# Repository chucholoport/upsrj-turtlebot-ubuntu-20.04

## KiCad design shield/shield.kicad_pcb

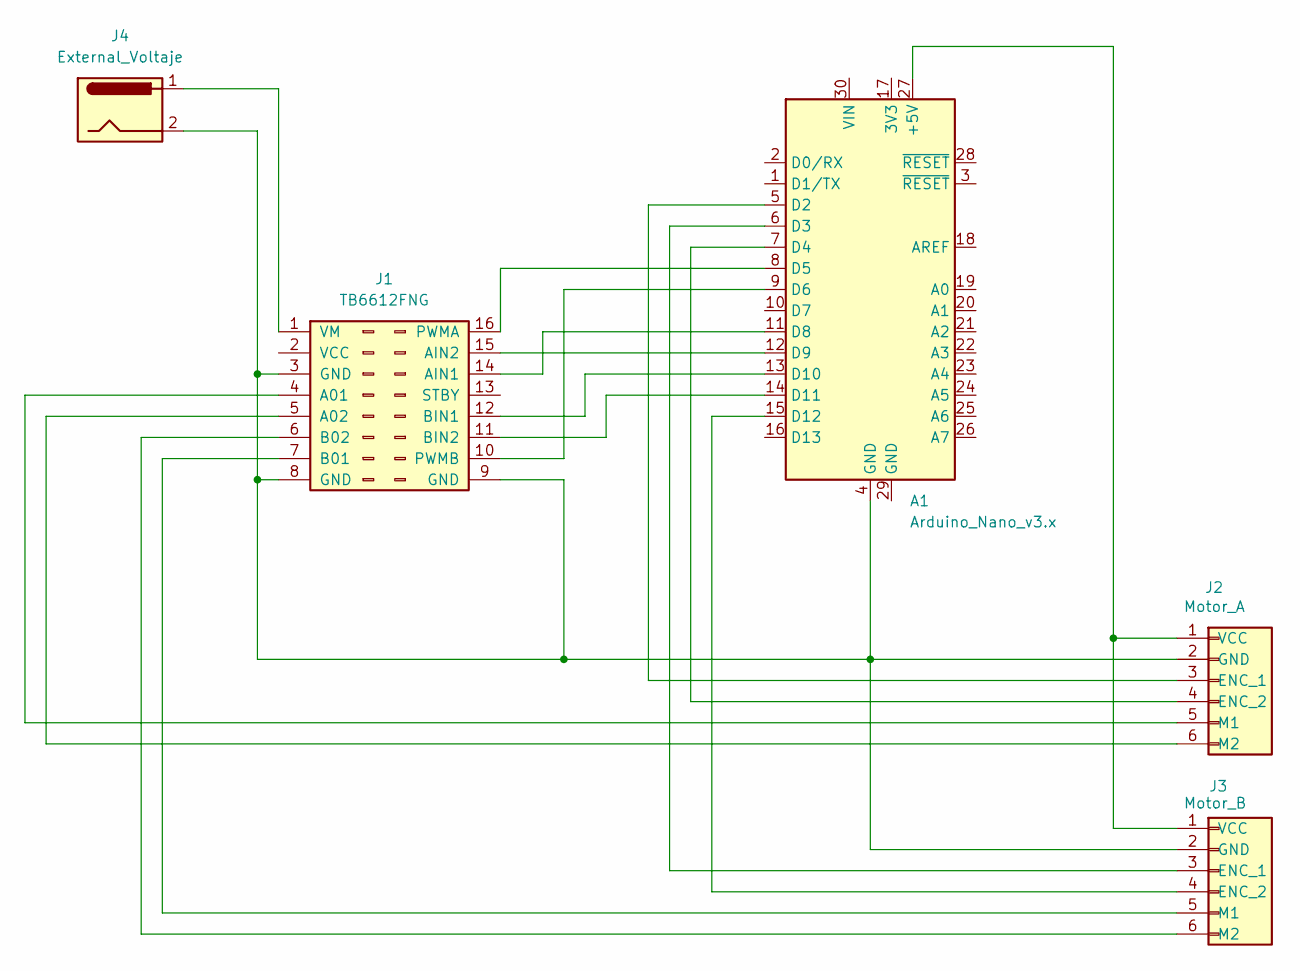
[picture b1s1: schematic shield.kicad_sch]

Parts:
A1: Arduino_Nano_v3.x; Arduino_Nano_WithMountingHoles
J1: TB6612FNG
J2: Motor_A; TerminalBlock_4Ucon_1x06_P3.50mm_Horizontal
J3: Motor_B; TerminalBlock_4Ucon_1x06_P3.50mm_Horizontal
J4: External_Voltaje; BarrelJack_Horizontal

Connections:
unnamed: A1.27 (+5V), J2.1 (VCC), J3.1 (VCC)
unnamed: A1.5 (D2), J2.3 (ENC_1)
unnamed: A1.6 (D3), J3.3 (ENC_1)
unnamed: A1.7 (D4), J2.4 (ENC_2)
unnamed: A1.8 (D5), J1.16 (PWMA)
unnamed: A1.9 (D6), J1.10 (PWMB)
unnamed: A1.11 (D8), J1.14 (AIN1)
unnamed: A1.12 (D9), J1.15 (AIN2)
unnamed: A1.13 (D10), J1.12 (BIN1)
unnamed: A1.14 (D11), J1.11 (BIN2)
unnamed: A1.15 (D12), J3.4 (ENC_2)
unnamed: J1.4 (A01), J2.5 (M1)
unnamed: J1.5 (A02), J2.6 (M2)
unnamed: J1.7 (B01), J3.5 (M1)
unnamed: J1.6 (B02), J3.6 (M2)
unnamed: J1.1 (VM), J4.1
unnamed: A1.4 (GND), J1.3 (GND), J1.8 (GND), J1.9 (GND), J2.2 (GND), J3.2 (GND), J4.2

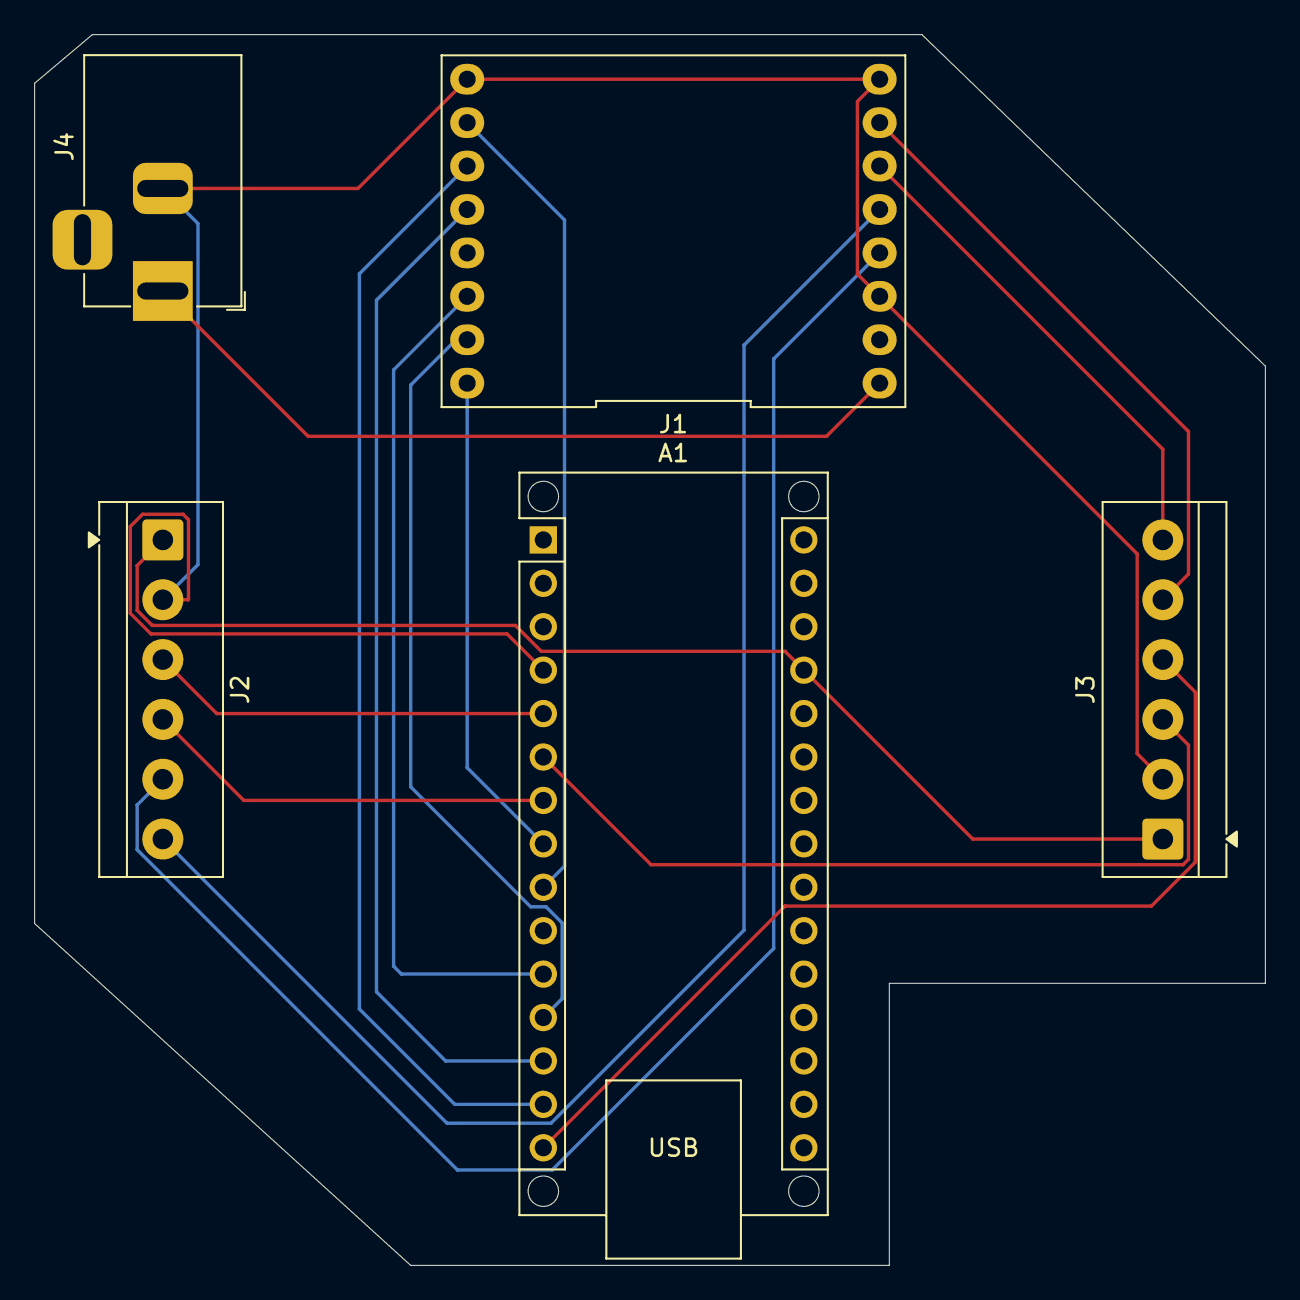
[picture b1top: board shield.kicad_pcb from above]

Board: 2 copper layers, 72.0 x 72.0 mm, 5 parts (0 on the bottom side), 17 nets.

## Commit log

2025-11-21 initial commit: install & remote connection docs
2025-11-21 turtlesim node & teleop_keyboard
2025-11-26 submodules: main package & arduino sketchbook
2025-11-26 encoder motor shield
2026-01-31 install browser script
2026-02-13 turtle robot chasis
2026-02-15 hector slam & automations
2026-02-15 hector slam test fix
